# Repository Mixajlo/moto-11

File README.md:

# moto-11

A modular **ESP32 smart-cockpit, accessory, and security system** for a 2013 Suzuki
V-Strom DL650 — hardware, firmware, harness, and documentation in one repository.

The guiding philosophy is **"fairings off once"**: provision generously now, upgrade in
place later. The ESP32 owns all bike logic; a tablet is a thin display; the phone handles
navigation and connectivity.

---

## What it is

`moto-11` turns the bike into a programmable platform without making any consumer device a
single point of failure:

- **Bike-side controller** — an ESP32-WROOM-32D that is always-hot, deep-sleeps when parked,
  and wakes on ignition. It is the single source of truth for relay control, sensing,
  load management, security, and the parked sentinel.
- **Dashboard** — an Android tablet acting as a *thin* BLE display and an Android Auto
  receiver. UI only; it never decides anything.
- **Phone** — navigation, connectivity, and the BLE relay that drains the bike's event queue
  when it's parked out of network range.

It also folds in the unglamorous-but-important electrical work: a series R/R charging upgrade,
relieving the notorious headlight-through-the-starter-switch wiring, accessory switching via a
relay box driven by a ULN2803, and battery/charging telemetry from an INA226.

## Status

**Early development.** OTA firmware (WiFi + ArduinoOTA + heartbeat) is proven on the bench
across both ESP units. Relay control and the **engine-run supervisor** are in and
bench-validated: a `RelayController` drives the four ULN2803 coil enables (fail-OFF at boot),
a serial/Telnet **bench console** actuates them by hand, and the supervisor runs the power
state machine — `SLEEP → ARMED → RUNNING ⇄ POWERED` (+ `OFF_DELAY`) with ignition-as-master,
a battery backstop, and a charge-health warning — driven by simulated sensors and covered by
unit tests. Next firmware milestone: the real **INA3221** driver + PC817 ignition-sense (then
flip `sim real`), and load-shedding. Hardware is at the bench-prototyping stage (KiCad schematic
+ first-pass PCB). See `docs/adr/` for the decisions made so far.

## Architecture

```
        ┌─────────────┐    BLE     ┌──────────────────────┐
        │   ESP32     │◄──────────►│  Tablet (thin UI +   │
        │ authoritative│            │  Android Auto recv)  │
        │ controller   │            └──────────────────────┘
        └──────┬───────┘                       ▲ projects
   I²C / GPIO / │ relays                        │ Android Auto
  ┌─────────────┼───────────────┐        ┌──────┴──────┐
  │ INA226  IMU  ULN2803  opto   │        │   Phone     │
  │ relay box   master relay     │        │ nav + relay │
  └──────────────────────────────┘        └─────────────┘
```

The ESP runs the bike; the tablet renders; the phone connects. A tablet reboot or removal
degrades only the UI, never the bike's function. Full reasoning is in
[`docs/adr/0001`](docs/adr/0001-esp32-authoritative-controller.md).

## Repository layout

```
moto-11/
├── CLAUDE.md          # project context for Claude Code (read first)
├── firmware/          # PlatformIO ESP32 project        (MIT)
│   ├── platformio.ini
│   ├── src/main.cpp
│   └── include/secrets.h.example
├── hardware/          # KiCad / relay-box as-built       (CERN-OHL-P)
├── harness/           # WireViz source + rendered output
├── docs/              # design docs + decision records    (CC-BY-4.0)
│   ├── electrical-plan.html
│   ├── wiring-schematic.html
│   └── adr/
└── app/               # future tablet / Android Auto app
```

## Hardware

| Area            | Choice                                                              |
|-----------------|--------------------------------------------------------------------|
| Controller      | ESP32-WROOM-32D (×2: bench twin + bike unit)                        |
| Charging        | Series R/R (Shindengen SH775 / SH847); stock stator, measured first |
| Accessory switch| Pre-wired 4-relay / 6-fuse box, gated by an external master relay   |
| Coil driver     | ULN2803A (low-side, internal flyback)                              |
| Sensing         | INA226 (bus voltage) + PC817 opto-isolated 12 V inputs + 6-axis IMU |
| Dashboard       | Android tablet (Galaxy Tab Active5 target) + phone                 |

The authoritative electrical design is in `docs/electrical-plan.html` (23 sections) and
`docs/wiring-schematic.html` (single-sheet wiring + ULN2803 driver detail).

## Getting started (firmware)

### Prerequisites
- [VS Code](https://code.visualstudio.com/) with the **PlatformIO IDE** extension
- **Silicon Labs CP210x USB-to-UART driver** (the ESP boards use a CP2102 — without it Windows
  shows no COM port)
- Git

### Clone and open
```bash
git clone https://github.com/<you>/moto-11.git
```
Open the **`firmware/`** subfolder in VS Code (`File → Open Folder → moto-11/firmware`).
PlatformIO expects `platformio.ini` at the root of the opened folder, so open `firmware/`
directly — not the repo root. (Git still tracks the whole repo.) On the first build,
PlatformIO downloads the ESP32 toolchain and framework; let it finish.

### Configure secrets
Copy the template and fill it in — it is gitignored, so your credentials never reach the repo:
```bash
cp include/secrets.h.example include/secrets.h
```
Set `WIFI_SSID`, `WIFI_PASS`, and an `OTA_PASS`. The `OTA_PASS` must match the `--auth=` value
in `platformio.ini`. Avoid `%` and `$` in the OTA password (the config parser treats them
specially).

### Build, flash, monitor
One codebase builds two devices via separate environments (`bench` / `bike`), distinguished by
`DEVICE_NAME`. First flash of each device is over USB:
```bash
pio run -e bench                 # build
pio run -e bench -t upload       # flash over USB
pio device monitor               # serial logs @ 115200
```
Swap `bench` → `bike` for the second unit. (In VS Code, the PlatformIO **Project Tasks** panel
exposes Build / Upload / Monitor per environment — use those rather than the status-bar buttons,
which act on whatever environment is selected.)

### OTA updates
After the first USB flash, update wirelessly:
```bash
pio run -e bench_ota -t upload
```
Set the device's IP (from the serial log) as `upload_port` in the `*_ota` environment if the
`.local` mDNS name doesn't resolve on your OS.

### Windows OTA gotcha
ArduinoOTA needs the ESP to open a connection *back* to your PC. Two things block this on
Windows:
- **Extra network adapters** (WSL/Hyper-V `vEthernet`, VMware, VirtualBox, VPN) — espota can
  advertise the wrong host IP. Disable them so only your real LAN/Wi-Fi adapter is active.
- **A third-party antivirus firewall** — independent of the Windows firewall; pause its network
  shield for the push.

Symptom is `Authenticating…OK` followed by `Waiting for device… No response`. See
[`docs/adr/0008`](docs/adr/0008-ota-ab-rollback.md).

## Documentation

- **[Bench relay guide](https://mixajlo.github.io/moto-11/bench-relay-guide.html)** —
  step-by-step: flash the firmware and click the relays on the bench (just an ESP + USB to
  start). Good first hands-on walkthrough. (Source: `docs/bench-relay-guide.html`.)
- **Design docs** — published via **GitHub Pages** from `/docs`:
  [home](https://mixajlo.github.io/moto-11/),
  [electrical plan](https://mixajlo.github.io/moto-11/electrical-plan.html),
  [wiring schematic](https://mixajlo.github.io/moto-11/wiring-schematic.html).
- **Decision records** (`docs/adr/`) — the *why* behind every major choice, Nygard-format.
- **`CLAUDE.md`** — the condensed project brief; also what Claude Code reads on startup.

## Design principles

- **Colourblind-safe output, always.** Every diagram, chart, and UI uses the Okabe-Ito palette
  and never encodes meaning by colour alone — colour is always paired with line pattern and a
  text label. The maintainer is colourblind; this is a hard constraint.
- **Fail-safe by direction.** Accessories fail **OFF** (safe when the ESP dies); headlights fail
  **ON**. Safety-critical lighting is never solely behind the controller.
- **Bench-twin-first.** Every change is proven on the bench twin before it reaches the bike.

## Licensing

This repo is multi-licensed by content type:

| Path         | License        |
|--------------|----------------|
| `firmware/`  | MIT            |
| `hardware/`  | CERN-OHL-P-2.0 |
| `harness/`   | CERN-OHL-P-2.0 |
| `docs/`      | CC-BY-4.0      |

Full texts live in `LICENSES/`. SPDX identifiers in file headers make this machine-readable;
the [REUSE](https://reuse.software) tool lints it.

## Disclaimer

This project modifies a motorcycle's electrical, charging, and lighting systems. Do this only
if you understand the risks — incorrect wiring can damage the bike, the battery, or yourself,
and some changes (e.g. lighting behaviour) may be subject to local road regulations. Use at your
own risk. Not affiliated with or endorsed by Suzuki.

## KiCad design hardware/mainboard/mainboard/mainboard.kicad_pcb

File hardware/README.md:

<!-- SPDX-License-Identifier: CERN-OHL-P-2.0 -->
# moto-11 — hardware

KiCad designs and as-built notes for the bike electronics. Licensed **CERN-OHL-P-2.0**
(permissive open hardware) — full text in [`../LICENSES/`](../LICENSES/).

> **Hardware safety:** this drives a motorcycle's 12 V electrical system. Nothing here is
> proven until it's bench-tested per the [bench relay guide](../docs/bench-relay-guide.html).
> Fail-safe direction is non-negotiable: accessories fail **OFF**, headlights fail **ON**.

## Boards

| Board | What it is | Status |
|-------|-----------|--------|
| [`mainboard/`](mainboard/) | ESP32-DevKitC carrier + ULN2803 coil driver + sensing front-end (INA3221, PC817 opto, MPU-6050 IMU) + connectors. Drives the **existing** pre-wired relay/fuse box; it does **not** carry load current. Master relay + at most **4 relay outputs** (OUT1–OUT4). | ✅ v1 laid out, pre-fab reviewed, ready to order |
| [`pwm-board/`](pwm-board/) | Expansion on the mainboard's J6 I²C header: PCA9685 (0x41) → 2× TC4427A → 4× AOD4184A low-side MOSFETs, **8 A each**, PWM for heated grips/seat (OUT5–OUT8), fused per channel, fed from the master-gated box output ([ADR-0022](../docs/adr/0022-pwm-expansion-board.md)). | ✅ v1 laid out, ordered with the mainboard; untested hardware |

The pre-wired 4-relay / 6-fuse box and the external master relay stay as discrete parts — the
mainboard is the brain that drives their coils and senses the bus. High load current (fog,
grips, tablet) never flows through this PCB.

## How this is organised

Per the chosen workflow, the design is captured as a **text design package** first, then drawn
in KiCad from it:

- [`mainboard/01-schematic-spec.md`](mainboard/01-schematic-spec.md) — the schematic as a
  component list + net-by-net connection table. This is the source of truth for capture.
- [`mainboard/02-bom.csv`](mainboard/02-bom.csv) — bill of materials with part numbers.
- [`mainboard/03-design-rules.md`](mainboard/03-design-rules.md) — board stackup, trace widths
  (sized from real currents), clearances, connectors, mechanical.
- [`mainboard/04-kicad-guide.md`](mainboard/04-kicad-guide.md) — step-by-step to turn the spec
  into a KiCad schematic + PCB, with DRC and fab outputs.

KiCad project files (`*.kicad_pro/_sch/_pcb`) land in `mainboard/` once capture begins.

## Toolchain

**KiCad 10.0.3** is installed on the build machine. Start with
[`04-kicad-guide.md`](mainboard/04-kicad-guide.md). The capture/layout workflow is stable across
KiCad 8–10, so the guide applies regardless of minor version.

## Cross-references

- GPIO pin map: [ADR-0009](../docs/adr/0009-gpio-pin-map.md) (this board adds two pins — see the
  schematic spec's *open decisions*).
- Coil driver rationale: [ADR-0003](../docs/adr/0003-uln2803-coil-driver.md).
- Master-relay gating / fail-safe: [ADR-0004](../docs/adr/0004-master-relay-gating-and-failon-headlights.md).
- Sensing: [ADR-0005](../docs/adr/0005-ina226-sensing.md).
- Authoritative electrical design: [`../docs/electrical-plan.html`](../docs/electrical-plan.html)
  and [`../docs/wiring-schematic.html`](../docs/wiring-schematic.html).

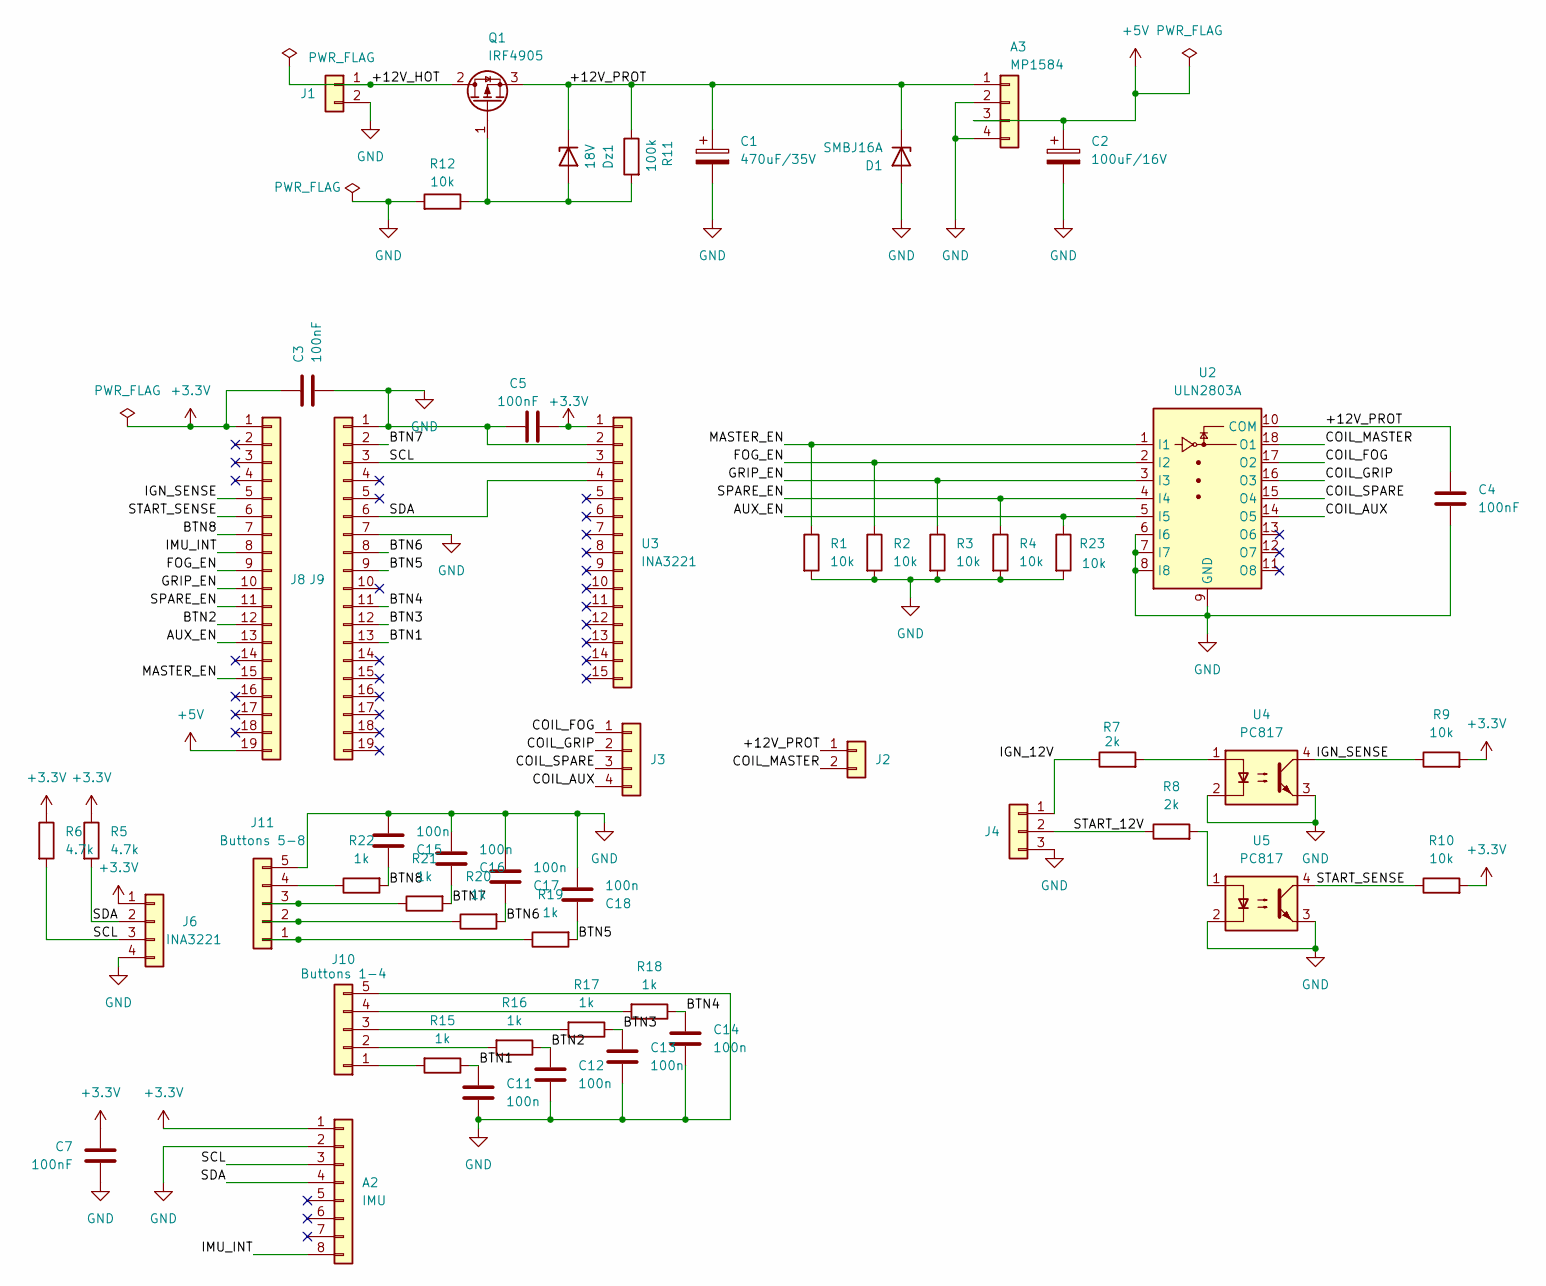
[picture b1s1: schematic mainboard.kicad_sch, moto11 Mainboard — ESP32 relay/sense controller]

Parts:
A2: IMU; GY-521_Module_20.8x15.9mm
A3: MP1584; MP1584_Module_22.5x17.2mm
C1: 470uF/35V; CP_Radial_D8.0mm_P3.50mm
C2: 100uF/16V; CP_Radial_D6.3mm_P2.50mm
C3, C4, C5, C7: 100nF; C_1206_3216Metric; LCSC C24497
C11, C12, C13, C14, C15, C16, C17, C18: 100n; C_1206_3216Metric; LCSC C24497
D1: SMBJ16A; D_SMB; LCSC C19077571
Dz1: 18V; D_DO-35_SOD27_P7.62mm_Horizontal
J1: TerminalBlock_MaiXu_MX126-5.0-02P_1x02_P5.00mm
J2: Master relay; TerminalBlock_MaiXu_MX126-5.0-02P_1x02_P5.00mm
J3: Relay box; TerminalBlock_MaiXu_MX126-5.0-04P_1x04_P5.00mm
J4: TerminalBlock_MaiXu_MX126-5.0-03P_1x03_P5.00mm
J6: INA3221; PinHeader_1x04_P2.54mm_Vertical
J8, J9: ESP32; PinSocket_1x19_P2.54mm_Vertical
J10: Buttons 1-4; JST_XH_B5B-XH-A_1x05_P2.50mm_Vertical
J11: Buttons 5-8; JST_XH_B5B-XH-A_1x05_P2.50mm_Vertical
Q1: IRF4905; TO-220-3_Vertical
R1, R2, R3, R4, R9, R10, R12, R23: 10k; R_1206_3216Metric; LCSC C17902
R5, R6: 4.7k; R_1206_3216Metric; LCSC C17936
R7, R8: 2k; R_1206_3216Metric; LCSC C17944
R11: 100k; R_1206_3216Metric; LCSC C17900
R15, R16, R17, R18, R19, R20, R21, R22: 1k; R_1206_3216Metric; LCSC C4410
U2: ULN2803A; DIP-18_W7.62mm_Socket
U3: INA3221; INA3221_Module_38.1x31.6mm
U4, U5: PC817; DIP-4_W7.62mm

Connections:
+3.3V: A2.1, C3.1, C5.2, C7.1, J6.1, J8.1, R5.1, R6.1, R9.2, R10.2, U3.1
+5V: A3.3, C2.1, J8.19
/+12V_HOT: J1.1, Q1.2 (D)
/+12V_PROT: A3.1, C1.1, C4.1, D1.1 (K), Dz1.1 (K), J2.1, Q1.3 (S), R11.1, U2.10 (COM)
/AUX_EN: J8.13, R23.1, U2.5 (I5)
/BTN1: C11.1, J9.13, R15.1
/BTN2: C12.1, J8.12, R16.1
/BTN3: C13.1, J9.12, R17.1
/BTN4: C14.1, J9.11, R18.1
/BTN5: C18.1, J9.9, R19.2
/BTN6: C17.1, J9.8, R20.2
/BTN7: C16.1, J9.2, R21.2
/BTN8: C15.1, J8.7, R22.2
/COIL_AUX: J3.4, U2.14 (O5)
/COIL_FOG: J3.1, U2.17 (O2)
/COIL_GRIP: J3.2, U2.16 (O3)
/COIL_MASTER: J2.2, U2.18 (O1)
/COIL_SPARE: J3.3, U2.15 (O4)
/FOG_EN: J8.9, R2.1, U2.2 (I2)
/GRIP_EN: J8.10, R3.1, U2.3 (I3)
/IGN_12V: J4.1, R7.1
/IGN_SENSE: J8.5, R9.1, U4.4
/IMU_INT: A2.8, J8.8
/MASTER_EN: J8.15, R1.1, U2.1 (I1)
/SCL: A2.3, J6.3, J9.3, R6.2, U3.3
/SDA: A2.4, J6.2, J9.6, R5.2, U3.4
/SPARE_EN: J8.11, R4.1, U2.4 (I4)
/START_12V: J4.2, R8.1
/START_SENSE: J8.6, R10.1, U5.4
GND: A2.2, A3.2, A3.4, C1.2, C2.2, C3.2, C4.2, C5.1, C7.2, C11.2, C12.2, C13.2, C14.2, C15.2, C16.2, C17.2, C18.2, D1.2 (A), J1.2, J4.3, J6.4, J9.1, J9.7, J10.5, J11.5, R1.2, R2.2, R3.2, R4.2, R12.2, R23.2, U2.6 (I6), U2.7 (I7), U2.8 (I8), U2.9 (GND), U3.2, U4.2, U4.3, U5.2, U5.3
unnamed: Dz1.2 (A), Q1.1 (G), R11.2, R12.1
unnamed: J10.1, R15.2
unnamed: J10.2, R16.2
unnamed: J10.3, R17.2
unnamed: J10.4, R18.2
unnamed: J11.1, R19.1
unnamed: J11.2, R20.1
unnamed: J11.3, R21.1
unnamed: J11.4, R22.1
unnamed: R7.2, U4.1
unnamed: R8.2, U5.1

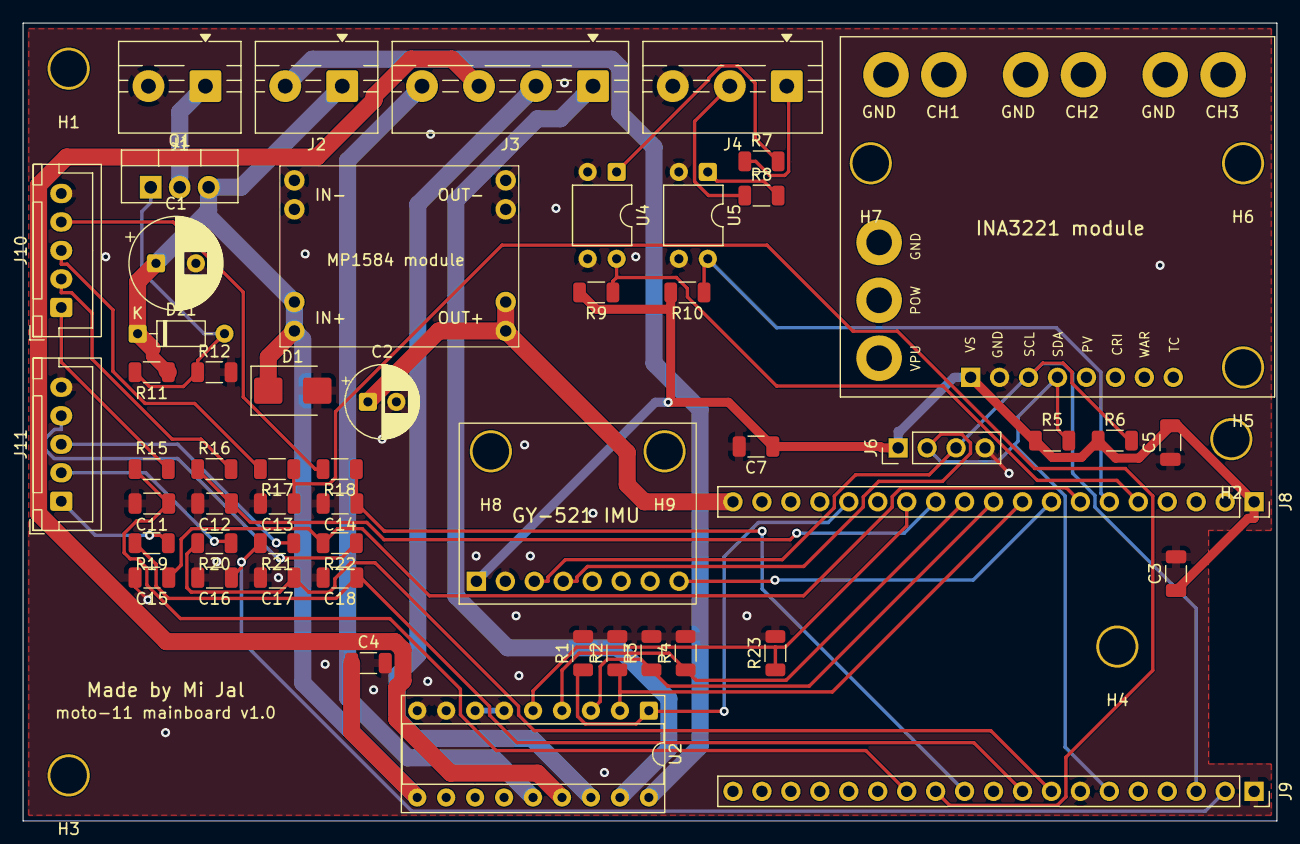
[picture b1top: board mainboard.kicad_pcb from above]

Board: 2 copper layers, 110.0 x 70.0 mm, 62 parts (0 on the bottom side), 41 nets.

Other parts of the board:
H1, H2, H3, H4, H5, H6, H7, H8, H9: MountingHole; MountingHole_3.2mm

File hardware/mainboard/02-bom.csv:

Ref,Qty,Value,Description,Footprint,Suggested part / MPN,Notes
A1,1,ESP32-DevKitC,ESP32-WROOM-32D dev board,Plugs into J8 + J9 or solders into the same holes,Espressif ESP32-DevKitC-32E,Reuse existing units; row spacing 25.40 mm confirmed from the module drawing
J8,1,1x19 socket,"OPTIONAL ESP32 socket, 3V3 side",Connector_PinSocket_2.54mm:PinSocket_1x19_P2.54mm_Vertical,generic 2.54mm female header,Optional: omit to solder A1 directly; A1 then cannot be swapped without desoldering and sits over H4 with only ~2.5 mm clearance (see H1-H4)
J9,1,1x19 socket,"OPTIONAL ESP32 socket, GND side",Connector_PinSocket_2.54mm:PinSocket_1x19_P2.54mm_Vertical,generic 2.54mm female header,Optional: see J8
A2,1,IMU,6-axis accel+gyro breakout GY-521 (MPU-6050),mainboard:GY-521_Module_20.8x15.9mm + 1x8 female header 2.54mm,GY-521 / MPU-6050,8-pin VCC GND SCL SDA XDA XCL AD0 INT; chip faces up with the header on the underside; INT->GPIO33; AD0 float = I2C addr 0x68
A3,1,Buck,MP1584EN mini buck module,"mainboard:MP1584_Module_22.5x17.2mm (8 pads, 4 pairs)",MP1584EN module,Pre-set 5.0V and verify before fitting
U2,1,ULN2803A,Darlington array 8ch low-side,Package_DIP:DIP-18_W7.62mm_Socket,ULN2803 DIP-18 (on hand) + 18-pin 7.62mm socket,Active-HIGH; COM to coil rail
U3,1,INA3221,3-channel bus voltage/current monitor breakout (CJMCU-3221),INA3221_Module_38.1x31.6mm (custom),CJMCU-3221 purple module,CH1=bus voltage; CH2/3 spare; 26V input max (clamp D3); socket via 1x8 VS/GND/SCL/SDA/PV/CRI/WAR/TC header; wire VS/GND/SCL/SDA only; addr 0x40
U4,1,PC817,Optocoupler single-channel,DIP-4_W7.62mm,Sharp PC817C,IGN 12V sense; keep THT DIP - the 7.62mm body delivers the >=4mm isolation creepage (ADR-0015). Do not swap to SOP-4
U5,1,PC817,Optocoupler single-channel,DIP-4_W7.62mm,Sharp PC817C,START/headlight 12V sense; keep THT DIP - see U4
Q1,1,IRF4905,Reverse-polarity protect,TO-220,Infineon IRF4905,DRAIN=+12V_HOT SOURCE=+12V_PROT (body-diode anode must face the battery; reversed = protection defeated). Symbol must be Q_PMOS_GDS to match pads 1=G 2=D 3=S
D1,1,SMBJ16A,TVS diode unidirectional 16V,SMB DO-214AA,Littelfuse SMBJ16A,Load-dump clamp on +12V_PROT; 26V max clamp keeps MP1584 under 28V
D3,1,P6KE18A,"TVS diode unidirectional, leaded (OFF-BOARD, not in schematic)","DO-15 leaded, wired at the module",P6KE18A,CH1 sense lead to GND; ~25 V max clamp keeps the INA3221 under its 26 V limit; verify datasheet when buying. Sense lead needs an inline fuse at the battery
Dz1,1,18V Zener,Gate-source clamp 0.5W,Diode_THT:D_DO-35_SOD27_P7.62mm_Horizontal,1N5248B,>14.4V idle while charging; <20V Vgs(max)
C1,1,470uF/35V,Bulk electrolytic,radial 8mm,generic 105C,On +12V_PROT
C2,1,100uF/16V,Bulk electrolytic,radial 6.3mm,generic 105C,On +5V
C3,1,100nF,Decoupling X7R,1206,generic,ESP power pin
C4,1,100nF,Decoupling X7R,1206,generic,ULN2803
C5,1,100nF,Decoupling X7R,1206,generic,INA3221
C7,1,100nF,Decoupling X7R,1206,generic,IMU
R1,1,10k,ULN input pulldown,1206,generic,MASTER_EN
R2,1,10k,ULN input pulldown,1206,generic,FOG_EN
R3,1,10k,ULN input pulldown,1206,generic,GRIP_EN
R4,1,10k,ULN input pulldown,1206,generic,SPARE_EN
R5,1,4.7k,I2C SDA pullup,1206,generic,to +3V3
R6,1,4.7k,I2C SCL pullup,1206,generic,to +3V3
R7,1,2k 0.25W,PC817 LED series,1206,LCSC C17944 (JLC basic),IGN 12V side ~5.4mA (was 2.2k; 2k is a JLC basic part); 1206 gives surge margin on the unprotected 12V sense
R8,1,2k 0.25W,PC817 LED series,1206,LCSC C17944 (JLC basic),START 12V side ~5.4mA; 1206 gives surge margin
R9,1,10k,GPIO34 pullup,1206,generic,opto output to +3V3
R10,1,10k,GPIO35 pullup,1206,generic,opto output to +3V3
R11,1,100k,Q1 gate-source,1206,generic,reverse-pol FET
R12,1,10k,Q1 gate pull-down,1206,generic,limits Dz1 current during load dump; required - do not reduce to 100R
J1,1,2-pos 5.0mm,Terminal block,TerminalBlock_MaiXu_MX126-5.0-02P_1x02_P5.00mm,MX126-5.0 or any 2P 5.0/5.08mm,+12V_HOT / GND
J2,1,2-pos 5.0mm,Terminal block,TerminalBlock_MaiXu_MX126-5.0-02P_1x02_P5.00mm,MX126-5.0 or any 2P 5.0/5.08mm,COIL_RAIL / GND
J3,1,4-pos 5.0mm,Terminal block,TerminalBlock_MaiXu_MX126-5.0-04P_1x04_P5.00mm,MX126-5.0 or any 4P 5.0/5.08mm,Coil outputs to 85 wires
J4,1,3-pos 5.0mm,Terminal block,TerminalBlock_MaiXu_MX126-5.0-03P_1x03_P5.00mm,MX126-5.0 or any 3P 5.0/5.08mm,IGN_12V / START_12V / SENSE_GND
J6,1,1x4 header,I2C expansion,2.54mm THT,generic,+3V3 SDA SCL GND
J10,1,1x5 JST-XH,Handlebar buttons group A,Connector_JST:JST_XH_B5B-XH-A_1x05_P2.50mm_Vertical,JST B5B-XH-A,BTN1-4 + GND (ADR-0014)
J11,1,1x5 JST-XH,Handlebar buttons group B,Connector_JST:JST_XH_B5B-XH-A_1x05_P2.50mm_Vertical,JST B5B-XH-A,BTN5-8 + GND
R15,1,1k,Button series (RC),1206,generic,BTN1; omit on bench
R16,1,1k,Button series (RC),1206,generic,BTN2; omit on bench
R17,1,1k,Button series (RC),1206,generic,BTN3; omit on bench
R18,1,1k,Button series (RC),1206,generic,BTN4; omit on bench
R19,1,1k,Button series (RC),1206,generic,BTN5; omit on bench
R20,1,1k,Button series (RC),1206,generic,BTN6; omit on bench
R21,1,1k,Button series (RC),1206,generic,BTN7; omit on bench
R22,1,1k,Button series (RC),1206,generic,BTN8; omit on bench
C11,1,100nF,Button RC to GND,1206,generic,BTN1
C12,1,100nF,Button RC to GND,1206,generic,BTN2
C13,1,100nF,Button RC to GND,1206,generic,BTN3
C14,1,100nF,Button RC to GND,1206,generic,BTN4
C15,1,100nF,Button RC to GND,1206,generic,BTN5
C16,1,100nF,Button RC to GND,1206,generic,BTN6
C17,1,100nF,Button RC to GND,1206,generic,BTN7
C18,1,100nF,Button RC to GND,1206,generic,BTN8
H1-H4,4,M3 hole,Mounting holes (board only),MountingHole_3.2mm,M3 screws + spacers,Drill the enclosure floor to match. H4 is under A1: unplug A1 to reach it. If A1 is soldered directly leave H4 empty or fit a low-profile screw first since it cannot be reached afterwards
H5-H7,3,M3 hole,Holes for fixing U3 to the board,MountingHole_3.2mm,M3 screws + spacers,Line up with the three holes on the INA3221 module. Spacer height must match the module's height on its header. Board only: U3's 8-pin header makes the connections
ENC1,1,Enclosure,"Sealed enclosure, internal min 118 x 75 x 40 mm",Off-board,"Any sealed ABS/PC box, IP65 or better",Minimum is measured inside at the PCB plane. Length includes the ESP antenna overhang. Height allows ~10 mm spacers + 1.6 mm PCB + ~16 mm tallest part + ~10 mm wire bend. Bike mounting hardware is left to the builder

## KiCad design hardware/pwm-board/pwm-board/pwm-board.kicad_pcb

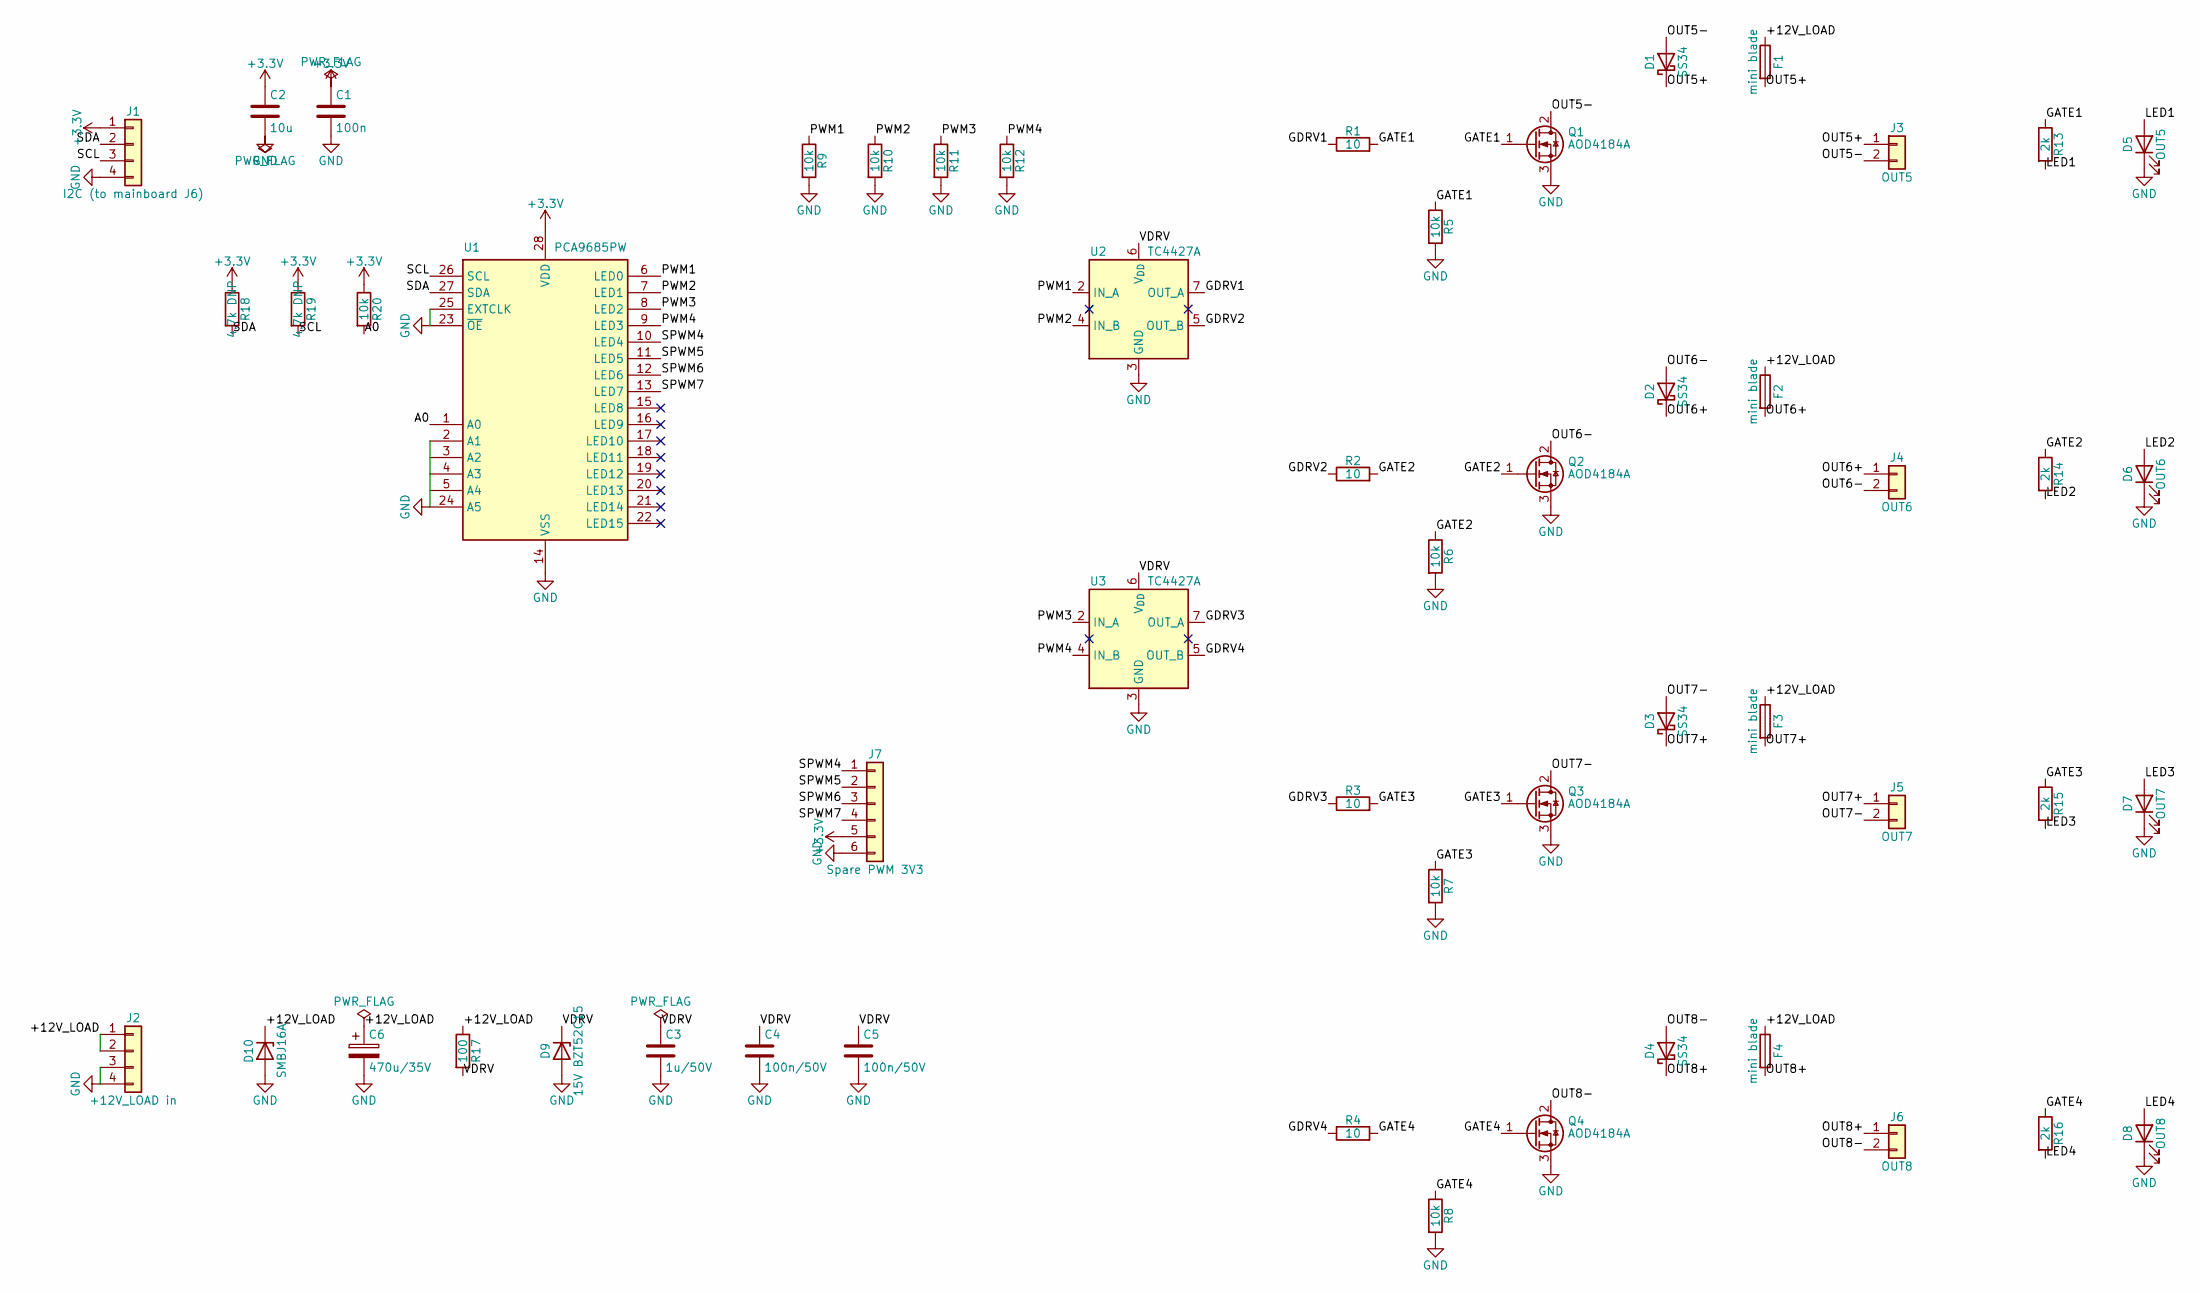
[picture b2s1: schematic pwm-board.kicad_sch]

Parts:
C1: 100n; C_1206_3216Metric; LCSC C24497
C2: 10u; C_1206_3216Metric; LCSC C13585
C3: 1u/50V; C_1206_3216Metric; LCSC C1848
C4, C5: 100n/50V; C_1206_3216Metric; LCSC C24497
C6: 470u/35V; CP_Radial_D8.0mm_P3.50mm
D1, D2, D3, D4: SS34; D_SMA; LCSC C8678
D5: OUT5; LED_1206_3216Metric; LCSC C965825
D6: OUT6; LED_1206_3216Metric; LCSC C965825
D7: OUT7; LED_1206_3216Metric; LCSC C965825
D8: OUT8; LED_1206_3216Metric; LCSC C965825
D9: 15V BZT52C15; D_SOD-123; LCSC C19077412
D10: SMBJ16A; D_SMB; LCSC C19077571
F1, F2, F3, F4: mini blade; Fuseholder_Blade_Mini_Keystone_3568
J1: I2C (to mainboard J6); JST_XH_B4B-XH-A_1x04_P2.50mm_Vertical
J2: +12V_LOAD in; TerminalBlock_MaiXu_MX126-5.0-04P_1x04_P5.00mm
J3: OUT5; TerminalBlock_MaiXu_MX126-5.0-02P_1x02_P5.00mm
J4: OUT6; TerminalBlock_MaiXu_MX126-5.0-02P_1x02_P5.00mm
J5: OUT7; TerminalBlock_MaiXu_MX126-5.0-02P_1x02_P5.00mm
J6: OUT8; TerminalBlock_MaiXu_MX126-5.0-02P_1x02_P5.00mm
J7: Spare PWM 3V3; JST_XH_B6B-XH-A_1x06_P2.50mm_Vertical
Q1, Q2, Q3, Q4: AOD4184A; TO-252-2; LCSC C99124
R1, R2, R3, R4: 10; R_1206_3216Metric; LCSC C17903
R5, R6, R7, R8, R9, R10, R11, R12, R20: 10k; R_1206_3216Metric; LCSC C17902
R13, R14, R15, R16: 2k; R_1206_3216Metric; LCSC C17944
R17: 100; R_1206_3216Metric; LCSC C17901
R18, R19: 4.7k DNP; R_1206_3216Metric
U1: PCA9685PW; TSSOP-28_4.4x9.7mm_P0.65mm; LCSC C2678753
U2, U3: TC4427A; SOIC-8_3.9x4.9mm_P1.27mm; LCSC C20551

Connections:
+3.3V: C1.1, C2.1, J1.1, J7.5, R18.1, R19.1, R20.1, U1.28 (VDD)
/+12V_LOAD: C6.1, D10.1 (K), F1.1, F2.1, F3.1, F4.1, J2.1, J2.2, R17.1
/A0: R20.2, U1.1 (A0)
/GATE1: Q1.1 (G), R1.2, R5.1, R13.1
/GATE2: Q2.1 (G), R2.2, R6.1, R14.1
/GATE3: Q3.1 (G), R3.2, R7.1, R15.1
/GATE4: Q4.1 (G), R4.2, R8.1, R16.1
/GDRV1: R1.1, U2.7 (OUT_A)
/GDRV2: R2.1, U2.5 (OUT_B)
/GDRV3: R3.1, U3.7 (OUT_A)
/GDRV4: R4.1, U3.5 (OUT_B)
/LED1: D5.2 (A), R13.2
/LED2: D6.2 (A), R14.2
/LED3: D7.2 (A), R15.2
/LED4: D8.2 (A), R16.2
/OUT5+: D1.1 (K), F1.2, J3.1
/OUT5-: D1.2 (A), J3.2, Q1.2 (D)
/OUT6+: D2.1 (K), F2.2, J4.1
/OUT6-: D2.2 (A), J4.2, Q2.2 (D)
/OUT7+: D3.1 (K), F3.2, J5.1
/OUT7-: D3.2 (A), J5.2, Q3.2 (D)
/OUT8+: D4.1 (K), F4.2, J6.1
/OUT8-: D4.2 (A), J6.2, Q4.2 (D)
/PWM1: R9.1, U1.6 (LED0), U2.2 (IN_A)
/PWM2: R10.1, U1.7 (LED1), U2.4 (IN_B)
/PWM3: R11.1, U1.8 (LED2), U3.2 (IN_A)
/PWM4: R12.1, U1.9 (LED3), U3.4 (IN_B)
/SCL: J1.3, R19.2, U1.26 (SCL)
/SDA: J1.2, R18.2, U1.27 (SDA)
/SPWM4: J7.1, U1.10 (LED4)
/SPWM5: J7.2, U1.11 (LED5)
/SPWM6: J7.3, U1.12 (LED6)
/SPWM7: J7.4, U1.13 (LED7)
/VDRV: C3.1, C4.1, C5.1, D9.1 (K), R17.2, U2.6 (V_{DD}), U3.6 (V_{DD})
GND: C1.2, C2.2, C3.2, C4.2, C5.2, C6.2, D5.1 (K), D6.1 (K), D7.1 (K), D8.1 (K), D9.2 (A), D10.2 (A), J1.4, J2.3, J2.4, J7.6, Q1.3 (S), Q2.3 (S), Q3.3 (S), Q4.3 (S), R5.2, R6.2, R7.2, R8.2, R9.2, R10.2, R11.2, R12.2, U1.2 (A1), U1.3 (A2), U1.4 (A3), U1.5 (A4), U1.14 (VSS), U1.23 (~OE), U1.24 (A5), U1.25 (EXTCLK), U2.3 (GND), U3.3 (GND)

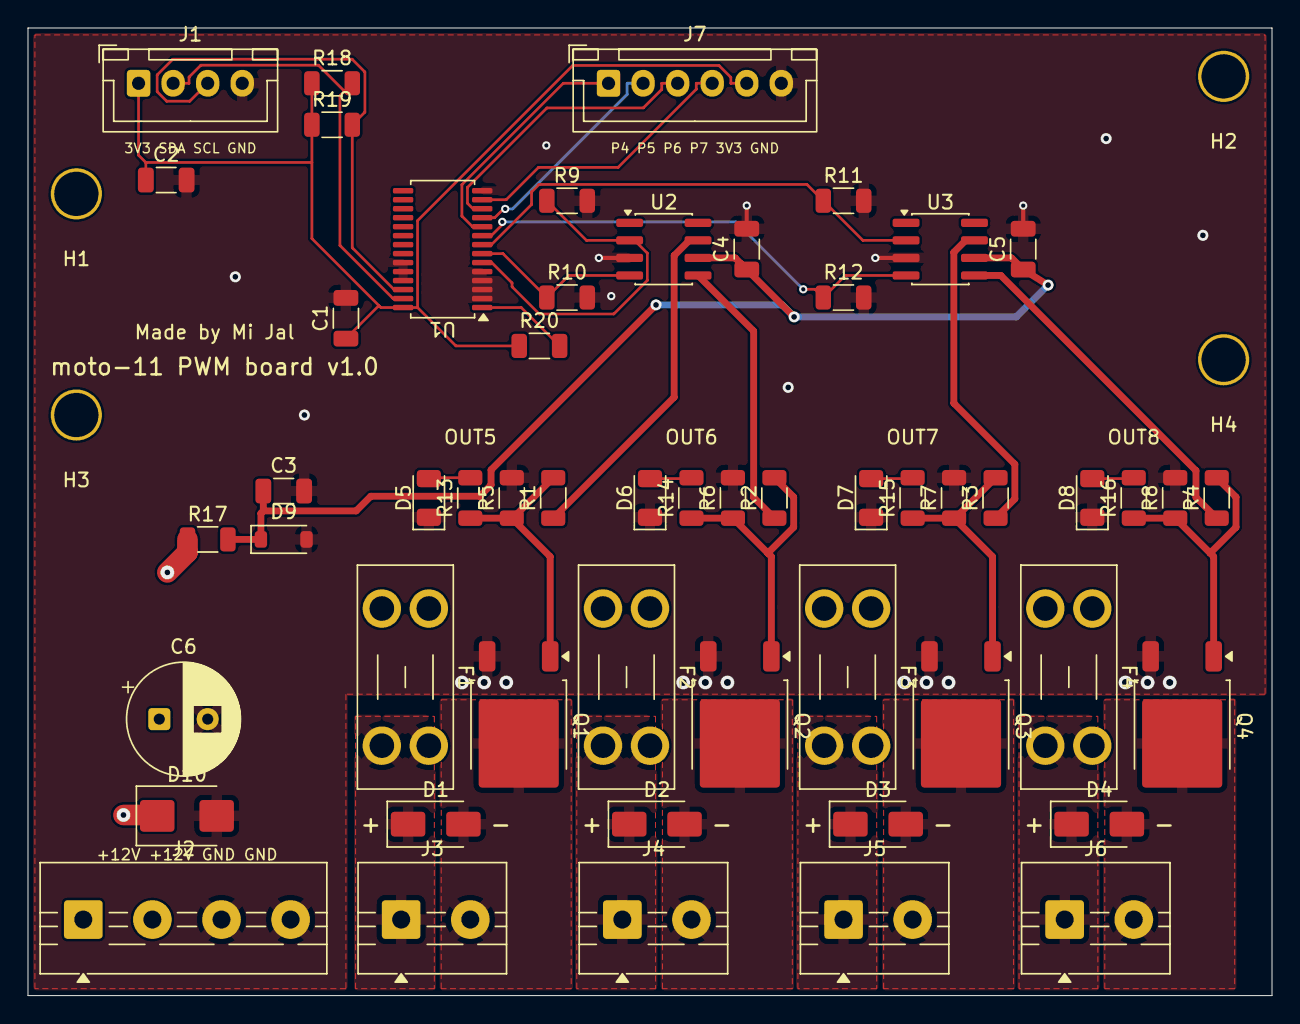
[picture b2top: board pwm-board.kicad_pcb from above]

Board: 2 copper layers, 90.0 x 70.0 mm, 58 parts (0 on the bottom side), 35 nets.

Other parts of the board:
H1, H2, H3, H4: MountingHole; MountingHole_3.2mm

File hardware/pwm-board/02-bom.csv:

Qty per board,Fitted by,LCSC,Part,Value / spec,Package / footprint,References,Notes
1,JLC,C2678753,PWM controller,PCA9685PW,TSSOP-28 (0.65 mm),U1,Extended part
2,JLC,C20551,Gate driver,TC4427AEOA (dual non-inverting),SOIC-8,U2 U3,Extended part
4,JLC,C99124,N-MOSFET,AOD4184A 40 V 7 mOhm,TO-252 (DPAK),Q1-Q4,Extended part
4,JLC,C8678,Schottky diode,SS34 3 A 40 V,SMA,D1-D4,"Flyback; NOT 1N4148"
1,JLC,C19077571,TVS diode,SMBJ16A (unidirectional),SMB,D10,Same as mainboard D1
1,JLC,C19077412,Zener,BZT52C15 15 V,SOD-123,D9,VDRV clamp
4,JLC,C965825,LED,XL-3216UGC green,1206,D5-D8,"Extended part; labelled OUT5-OUT8 on silk (meaning never by colour)"
1,JLC,C24497,Ceramic cap,100 nF 50 V X7R,1206,C1,
1,JLC,C13585,Ceramic cap,10 uF 50 V X5R,1206,C2,
1,JLC,C1848,Ceramic cap,1 uF 50 V X7R,1206,C3,
2,JLC,C24497,Ceramic cap,100 nF 50 V X7R,1206,C4 C5,
4,JLC,C17903,Resistor,10 R,1206,R1-R4,Gate series
9,JLC,C17902,Resistor,10 k,1206,R5-R12 R20,"Gate + input pull-downs, A0 pull-up"
4,JLC,C17944,Resistor,2 k,1206,R13-R16,"LED series, about 4.5 mA (was 1.5 k; 2 k is a JLC basic part)"
1,JLC,C17901,Resistor,100 R,1206,R17,"+12V_LOAD -> VDRV (was 47 R; 100 R halves the zener stress on a spike)"
2,not fitted,-,Resistor,4.7 k (DNP),1206,R18 R19,"Do not fit - mainboard R5/R6 pull up the I2C bus"
4,hand,-,Fuse holder,Keystone 3568 mini blade PCB,THT,F1-F4,"Exact part - footprint is specific; order from LCSC with the boards"
4+,hand,-,Mini blade fuse,sized to the load wire (e.g. 7.5 A grips),mini blade,(in F1-F4),
1,hand,-,Screw terminal,MaiXu MX126 4-pos 5.0 mm,THT,J2,"+12V_LOAD in: pins 1+2 = +12 V, 3+4 = GND"
4,hand,-,Screw terminal,MaiXu MX126 2-pos 5.0 mm (>=10 A/pin),THT,J3-J6,"OUT5-OUT8: pin 1 = +, pin 2 = -"
1,hand,-,Electrolytic cap,470 uF 35 V,radial 8 mm P3.5,C6,
1,hand,-,Connector,JST-XH 4-pin socket (owner's kit),2.50 mm THT,J1,"I2C to mainboard J6 (3V3, SDA, SCL, GND)"
1,hand,-,Connector,JST-XH 6-pin socket (owner's kit),2.50 mm THT,J7,"Spare PWM P4-P7 + 3V3 + GND, 3.3 V logic only"

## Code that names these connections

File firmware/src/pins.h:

// ===== pins.h — ESP32 GPIO map =====
// The single place that maps logical signals to physical ESP32 pins.
// Rationale and constraints are recorded in docs/adr/0009-gpio-pin-map.md.
//
// Relay enables are active-HIGH into the ULN2803A inputs. Every pin chosen
// here sits LOW at boot, so all relays stay OFF while the ESP boots — which
// matches the 10 kΩ pull-downs on the ULN inputs and the accessory fail-OFF rule.
//
// One exception to "no strapping pins" (ADR-0018): AUX_EN is GPIO 12 (MTDI), which
// selects the flash voltage at reset. LOW = 3.3 V flash, the right level for the
// WROOM-32D, and also relay-OFF; its 10 kΩ pull-down (R23) holds both. Never drive
// it HIGH before setup(), and never fit a pull-up on it.
#pragma once

#include <Arduino.h>

// --- Relay coil enables (ULN2803A inputs 1..5) ---
constexpr uint8_t PIN_MASTER_EN = 13;   // ULN ch1 -> J2: external master relay (gates the whole box)
constexpr uint8_t PIN_FOG_EN    = 25;   // ULN ch2 -> J3.1: box relay, fog lights
constexpr uint8_t PIN_GRIP_EN   = 26;   // ULN ch3 -> J3.2: box relay, heated grips
constexpr uint8_t PIN_SPARE_EN  = 27;   // ULN ch4 -> J3.3: box relay, spare load
constexpr uint8_t PIN_AUX_EN    = 12;   // ULN ch5 -> J3.4: box relay, aux load (strapping pin, see above)

// --- Inputs (opto-isolated 12 V sense; logic inverts: 12 V present -> LOW) ---
constexpr uint8_t PIN_IGN_SENSE   = 34; // ignition/run-sense; input-only + RTC (ext0 wake)
constexpr uint8_t PIN_START_SENSE = 35; // start-button / headlight-feed sense; input-only + RTC
constexpr uint8_t PIN_IMU_INT     = 33; // IMU wake-on-motion interrupt; RTC (deep-sleep wake)

// --- I2C bus (INA3221 bus-voltage sense + 6-axis IMU) ---
constexpr uint8_t PIN_I2C_SDA   = 21;
constexpr uint8_t PIN_I2C_SCL   = 22;

// --- Aux buttons (ADR-0014, ADR-0016): dry contacts, active-LOW with internal pull-up ---
// BTN1..BTN8; 7 used by the handlebar case + 1 spare. All pull-up-capable, no
// strapping/flash pins. In ring mode BTN5 is pulled low as a scan line, never driven
// high. Past 8 buttons -> MCP23017 on I2C (board rev, no re-wire).
constexpr uint8_t PIN_BTN[] = { 4, 14, 16, 17, 18, 19, 23, 32 };

// --- Onboard LED (heartbeat / bench relay-activity indicator) ---
constexpr uint8_t PIN_LED       = 2;

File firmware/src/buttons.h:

// ===== buttons.h — handlebar aux buttons (ADR-0014, ADR-0016) =====
// Dry-contact buttons, active-LOW with internal pull-ups, each input debounced. What
// an input does is runtime config, saved in NVS: its relay, and whether it is momentary
// (a press toggles the relay) or latching (the switch position sets the relay). A
// different switch set is then a console change, not a firmware change. `fire()` is
// also callable from the console (`btn press <n>`) so a mapping is bench-testable
// before the switches are wired.
//
// Ring mode, also saved in NVS, reads the case's factory-wired loop through BTN4-6
// (see button_ring.h) and reports its four buttons as BTN4-7. With one wire per button
// the same four buttons land on BTN4-7 directly, so the mapping carries over.
#pragma once

#include <Arduino.h>
#include "relays.h"

constexpr uint8_t BUTTON_COUNT = 8;   // BTN1..BTN8 (PIN_BTN[] in pins.h); 7 used + 1 spare

class Buttons {
public:
  void begin();                       // INPUT_PULLUP every BTN pin, load the saved settings
  void update();                      // scan + debounce; act on a settled change
  void fire(uint8_t idx);             // toggle button idx's mapped relay (0-based)

  // Validate + persist one input's action. RELAY_COUNT = unmapped; MASTER is refused.
  bool configure(uint8_t idx, RelayId relay, bool latching, const char** err = nullptr);
  void resetMapping();                // restore the firmware default mapping + persist

  void setRing(bool on);              // select + persist ring mode (not touched by resetMapping)
  bool ring() const { return ring_; }
  bool inRing(uint8_t idx) const;     // true if idx is currently read through the ring scan

  bool    pressed(uint8_t idx) const;  // current debounced state (true = pressed/closed)
  RelayId mapping(uint8_t idx) const;  // mapped relay, or RELAY_COUNT if unmapped
  bool    latching(uint8_t idx) const; // true = switch position sets the relay

private:
  struct Action { RelayId relay; bool latching; };

  void readRing(uint32_t now);        // advance the non-blocking ring scan
  void act(uint8_t idx, bool closed); // run the action for a settled change

  Action   action_[BUTTON_COUNT];
  bool     raw_[BUTTON_COUNT]        = { false };   // latest undebounced state
  bool     stable_[BUTTON_COUNT]     = { false };   // debounced "pressed?" state
  bool     lastRead_[BUTTON_COUNT]   = { false };   // last raw read
  uint32_t lastChange_[BUTTON_COUNT] = { 0 };       // millis of last raw change

  bool     ring_       = true;
  bool     scanning_   = false;       // true while BLACK is driven low
  uint32_t phaseStart_ = 0;           // millis the current scan phase began
  bool     idleWhite_  = false;       // idle sample, kept for the decode after the scan
  bool     idleBlack_  = false;
  bool     idleGreen_  = false;
};

extern Buttons Btns;

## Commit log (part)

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2026-06-19 Adding OTA to the device
2026-06-19 Add design docs
2026-06-19 Adding ADR files
2026-06-19 Adding README
2026-06-19 Adding index.html
2026-06-19 Adding relay support
2026-06-19 Adding aditional ADRs and kicad kickoff
2026-06-22 hardware(mainboard): complete schematic + first-pass PCB layout
2026-06-23 firmware: engine-run supervisor + sensors + gated debug logging
2026-06-23 docs: ADR-0012 (power model) + sync electrical-plan and CLAUDE
2026-06-23 fix(supervisor): remove charge-warning threshold overlap
2026-06-23 feat(console): show countdown to the next timed state change
2026-06-23 feat(supervisor): debounce + hysteresis on the charge-marginal warning
2026-06-23 test: Unity tests for the engine-run supervisor (run on the ESP)
2026-06-23 test: native (host) supervisor tests via g++/WSL
2026-06-23 docs: sync state machine to 5 states (POWERED) across the docs
2026-06-23 docs: Fig 2.1 off-delay shows 30 s default, not the 0-600 s range
2026-06-23 docs: ADR-0013 (runtime config via NVS/console) + ADR-0014 (aux buttons per-GPIO)
2026-06-25 feat(firmware): runtime config (NVS) + handlebar aux buttons
2026-06-25 hw(mainboard): custom INA3221 footprint + handlebar button connector

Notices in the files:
hardware/mainboard/mainboard/mainboard.kicad_pcb:
CERN-OHL-P-2.0 · github.com/Mixajlo/moto-11
